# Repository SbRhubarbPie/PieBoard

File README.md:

# PieBoard

A 100% custom keyboard made as a project for Hack Club's Highway to Undercity,
This keyboard has a standard 104 key layout with a 6.25u spacebar, I did this for keycap compatibility and because I really like full size keyboards for the numpad and immense macro potential. It features per key individually addressable LEDs (neopixel), as well as magnetic TPU feet for quick changing of height on the entirely 3d printed case. I also added a rotary encoder on the top right of the keyboard for media control as well as a screen for personalization and to display extra information.

I started this project because I wanted to make something with actual practical use while challenging myself to learn the depths of PCB design and get myself more familiar with coding as someone who mainly comes from 3d design. So far I am really satisfied with the results.

Full 3d model (step file) is available [here](https://drive.google.com/file/d/1Ark-gIqw4EnjqvL87gDNia2R5NBRhxoe/view) because github file size limits 

beware of making this project before I finish it and make fixes

| Name                            | Quanity Needed | Quantity Buying (Due to MOQs) | Source                  | Link                                                                                                                 | Price                      | Grand Total |
|---------------------------------|----------------|-------------------------------|-------------------------|----------------------------------------------------------------------------------------------------------------------|----------------------------|-------------|
| PCB                             | 1              | 5                             | JLCPCB                  |                                                                                                                      | 24.70 ($14.70 with coupon) |             |
| Shipping                        |                |                               | JLCPCB                  |                                                                                                                      | $27.19                     |             |
| Rotary Encoder                  | 1              | 1                             | LCSC                    | https://www.lcsc.com/product-detail/Rotary-Encoders_ALPSALPINE-EC11E153440D_C370992.html                             | $2.11                      |             |
| 100nF Capacitor                 | 1              | 100                           | LCSC                    | https://www.lcsc.com/product-detail/Multilayer-Ceramic-Capacitors-MLCC-SMD-SMT_YAGEO-CC0805KRX7R9BB104_C49678.html   | $0.45                      |             |
| 33Ω Resistor                    | 1              | 100                           | LCSC                    | https://www.lcsc.com/product-detail/Chip-Resistor-Surface-Mount_UNI-ROYAL-Uniroyal-Elec-0805W8F330JT5E_C17634.html   | $0.17                      |             |
| 5.1kΩ Resistor                  | 2              | 100                           | LCSC                    | https://www.lcsc.com/product-detail/Chip-Resistor-Surface-Mount_UNI-ROYAL-Uniroyal-Elec-0805W8F5101T5E_C27834.html   | $0.19                      |             |
| Resettable Fuse                 | 1              | 5                             | LCSC                    | https://www.lcsc.com/product-detail/Resettable-Fuses_Littelfuse-1206L050-15YR_C151162.html                           | $0.46                      |             |
| ESD & Surge Protector           | 1              | 5                             | LCSC                    | https://www.lcsc.com/product-detail/ESD-and-Surge-Protection-TVS-ESD_Nexperia-PRTR5V0U2X-215_C12333.html             | $ 0.46                     |             |
| 1N4148W Diode                   | 104            | 150                           | LCSC                    | https://lcsc.com/product-detail/Switching-Diodes_Jiangsu-Changjing-Electronics-Technology-Co-Ltd-1N4148W_C2099.html  | $1.38                      |             |
| Logic Level Shifter             | 1              | 5                             | LCSC                    | https://lcsc.com/product-detail/Buffers-Drivers-Receivers-Transceivers_Texas-Instruments-SN74LV1T34DBVR_C100024.html | $0.53                      |             |
| USB C Recepticle                | 1              | 5                             | LCSC                    | https://lcsc.com/product-detail/USB-Connectors_Korean-Hroparts-Elec-TYPE-C-31-M-12_C165948.html                      | $0.87                      |             |
| Neoleds                         | 104            | 110                           | LCSC                    | https://lcsc.com/product-detail/RGB-LEDs-Built-in-IC_OPSCO-Optoelectronics-SK6812MINI-E_C5149201.html                | $6.50                      |             |
| Screws                          | 12             | 50                            | LCSC                    | https://lcsc.com/product-detail/Screw-bolt_Tong-Ming-262514_C2931395.html                                            | $0.35                      |             |
| Shipping & Fees                 |                |                               | LCSC                    |                                                                                                                      | $12.29                     |             |
| Stabilizers                     | 1 Set of 8     | 1                             | Amazon                  | https://www.amazon.com/dp/B0B2RW12S2                                                                                 | $22.98                     |             |
| Keycaps                         | 1 Set          | 1                             | Amazon                  | https://www.amazon.com/dagaladoo-Printed-PBT-keycaps-Through-Keyboard/dp/B0CP7NZCQY?th=1                             | $25.64                     |             |
| Solder Paste                    | 1              | 1                             | Amazon                  | https://www.amazon.com/Essmetuin-Soldering-Electronics-soldering-Electrical/dp/B0BXM1GF3Y/131-1358947-9346814        | $8.99                      |             |
| Screen                          | 1              | 1                             | Aliexpress              | https://www.aliexpress.us/item/3256806315309280.html                                                                 | $1.95                      |             |
| 5x2 Magnets                     | 8              | 50                            | Aliexpress              | https://www.aliexpress.us/item/3256808695821393.html                                                                 | $3.62                      |             |
| USB C Cable                     | 1              | 1                             | Aliexpress              | https://www.aliexpress.us/item/3256808312113111.html                                                                 | $7.37                      |             |
| Heatset inserts M2, OD3.2, L3.5 | 12             | 50                            | Aliexpress              | https://www.aliexpress.us/item/3256803396040989.html                                                                 | $1.88                      |             |
| RP2350 Stamp                    | 1              | 1                             | Pimoroni                | https://shop.pimoroni.com/products/rp2350-stamp?variant=53521682530683                                               | $13.30                     |             |
| Shipping                        |                |                               | Pimoroni                |                                                                                                                      | $13.30                     |             |
| Keyswitches                     | 104            | 108                           | Kinetic Labs            | https://kineticlabs.com/switches/gateron/gateron-milky-yellow-pro-black-bottom-linear                                | $24.84                     |             |
| Shipping                        |                |                               | Kinetic Labs            |                                                                                                                      | $6.30                      |             |
| Some Wire (14-16 awg            | 1 foot ish?    |                               | my box of random things |                                                                                                                      | $0                         |             |
|                                 |                |                               |                         |                                                                                                                      |                            | 197.36      |

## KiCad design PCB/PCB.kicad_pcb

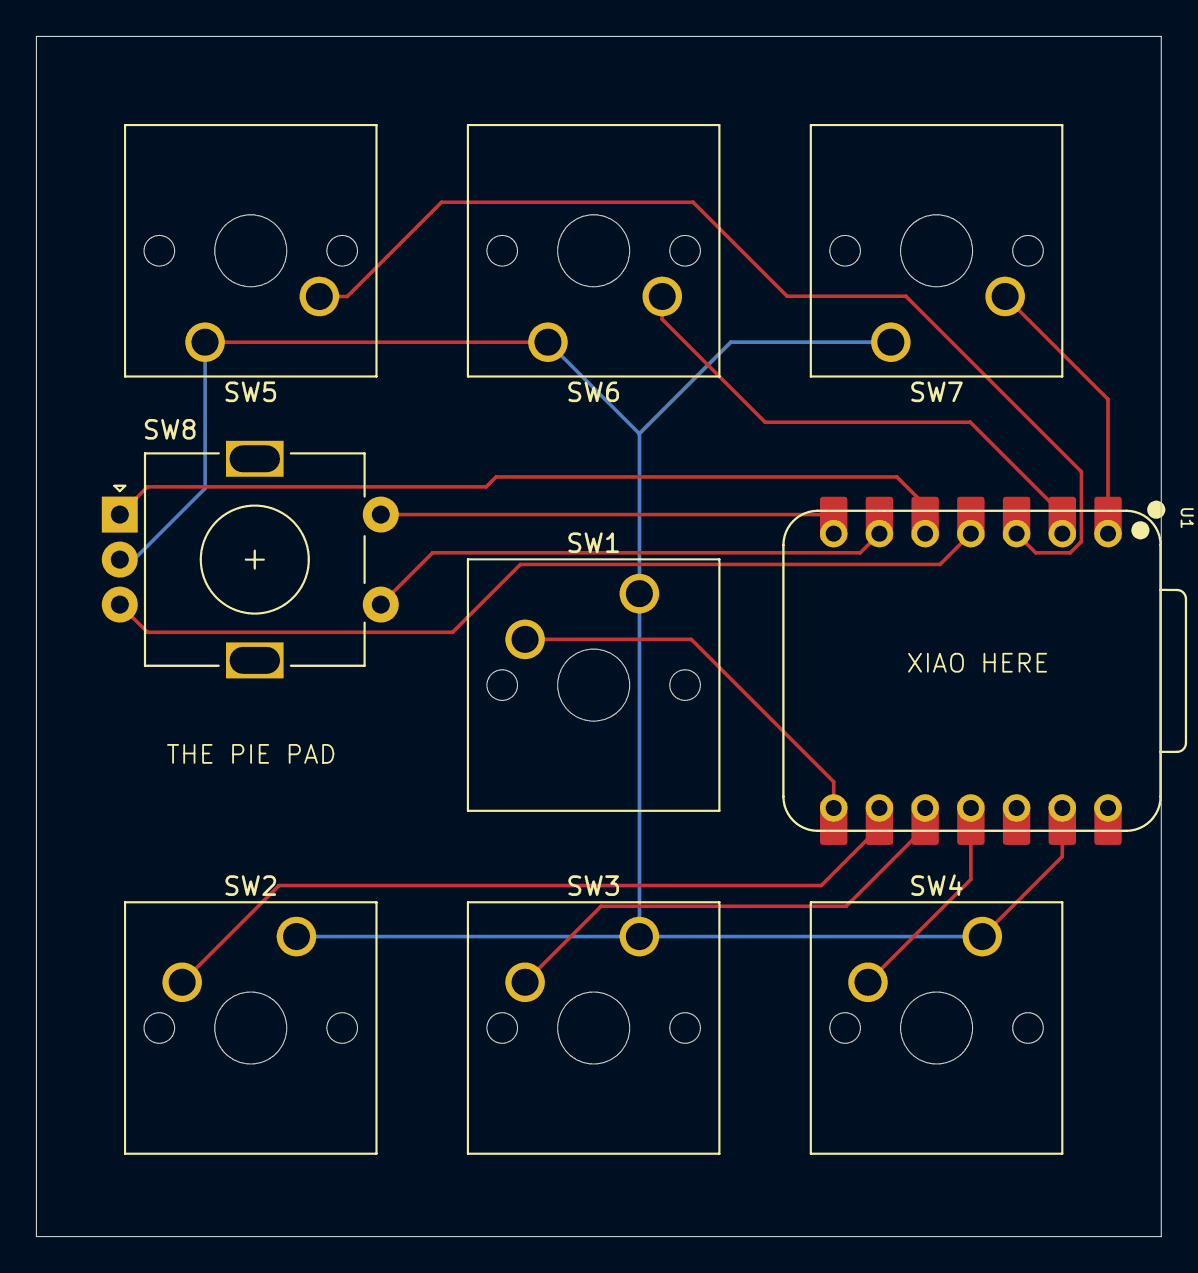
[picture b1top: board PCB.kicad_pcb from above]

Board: 2 copper layers, 62.5 x 66.7 mm, 9 parts (0 on the bottom side), 12 nets.

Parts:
SW1, SW2, SW3, SW4, SW5, SW6, SW7: SW_Push; SW_Cherry_MX_1.00u_PCB
SW8: RotaryEncoder_Switch; RotaryEncoder_Alps_EC11E-Switch_Vertical_H20mm
U1: XIAO-RP2040-DIP

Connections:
GND: SW1.1, SW2.1, SW3.1, SW4.1, SW5.1, SW6.1, SW7.1, SW8.C, U1.13 (GND)
unnamed: SW8.S2, U1.7 (GPIO0/TX)
unnamed: SW1.2, U1.8 (GPIO1/RX)
unnamed: SW2.2, U1.9 (GPIO2/SCK)
unnamed: SW4.2, U1.11 (GPIO3/MOSI)
unnamed: SW3.2, U1.10 (GPIO4/MISO)
unnamed: SW8.A, U1.5 (GPIO6/SDA)
unnamed: SW8.S1, U1.6 (GPIO7/SCL)
unnamed: SW7.2, U1.1 (GPIO26/ADC0/A0)
unnamed: SW6.2, U1.2 (GPIO27/ADC1/A1)
unnamed: SW5.2, U1.3 (GPIO28/ADC2/A2)
unnamed: SW8.B, U1.4 (GPIO29/ADC3/A3)

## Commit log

2025-06-08 Rename BOM.md to BOM.csv
2025-06-20 Add files via upload
    update to include neopixel decoupling caps
2025-06-20 Update BOM.csv
    add 10uf decoupling caps
2025-06-21 Update BOM.csv
    keyswitches out of stock from previous seller
2025-06-21 Update BOM.csv
    new final price with new keyswtich source
